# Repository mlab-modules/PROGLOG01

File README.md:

# PROGLOG01B - Small low-power open-source tool chain compatible FPGA

<!--- Lead --->
Module with a small programmable gate-array [ICE40UP5K](https://www.latticesemi.com/en/Products/FPGAandCPLD/iCE40UltraPlus).
<!--- ELead --->

The FPGA module compatible with fully open source toolchains like [symbiflow](https://symbiflow.github.io/).

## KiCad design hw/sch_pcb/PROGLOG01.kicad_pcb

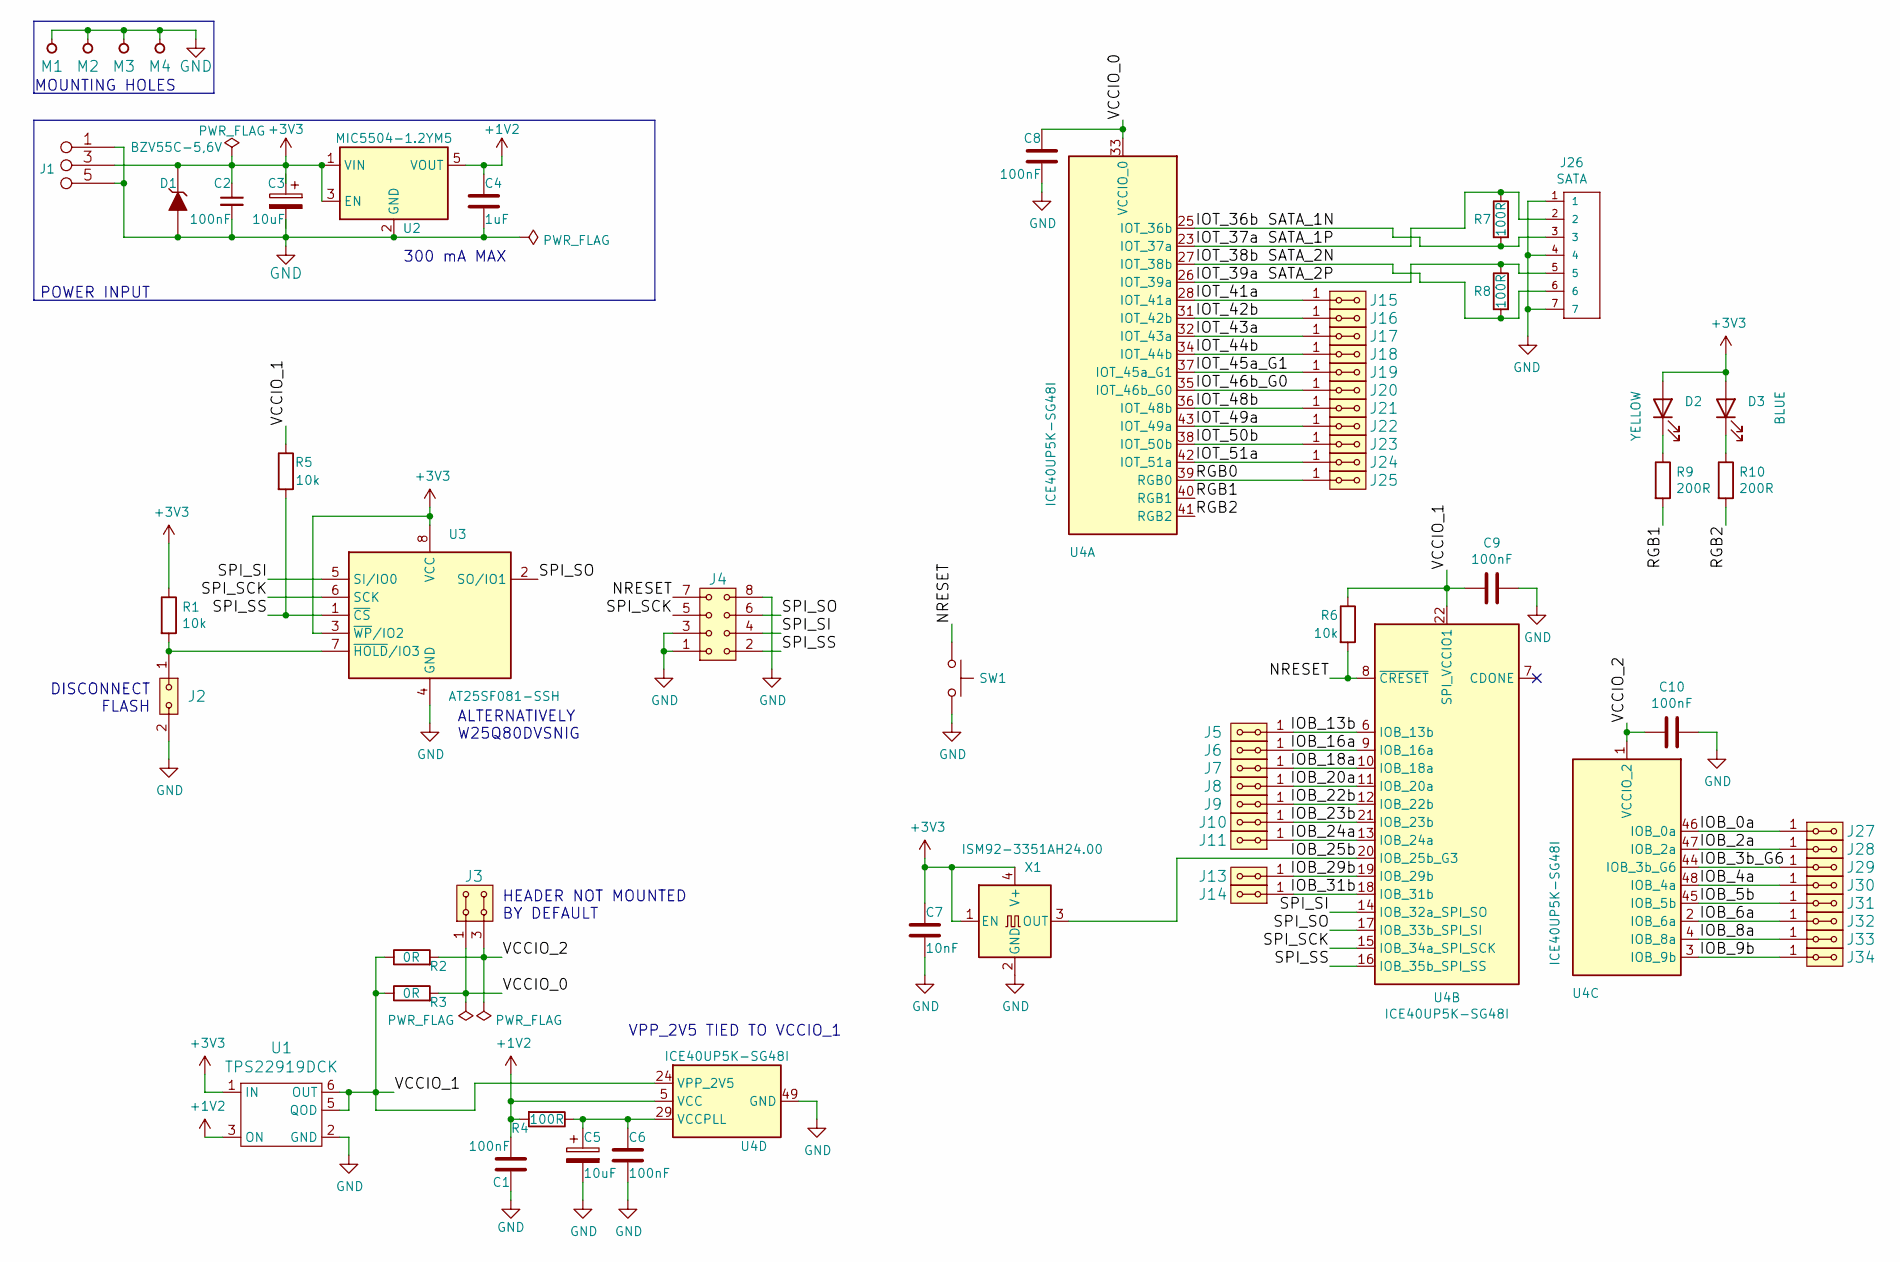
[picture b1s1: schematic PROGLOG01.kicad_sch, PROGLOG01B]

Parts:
C1, C2, C6, C8, C9, C10: 100nF; C_0805_2012Metric
C3, C5: 10uF; C_0805_2012Metric
C4: 1uF; C_0805_2012Metric
C7: 10nF; C_0805_2012Metric
D1: BZV55C-5,6V; Diode-MiniMELF_Standard
D2: YELLOW; LED_1206
D3: BLUE; LED_1206
J1: JUMP_3X2; Straight_2x03
J2: HEADER_2x01; Straight_2x01
J3: HEADER_2x02_PARALLEL; Straight_2x02
J4: HEADER_2x04; Straight_2x04
J5, J6, J7, J8, J9, J10, J11, J13, J14, J15, J16, J17, J18, J19, J20, J21, J22, J23, J24, J25, J27, J28, J29, J30, J31, J32, J33, J34: HEADER_2x01_PARALLEL; Straight_2x01
J26: SATA; MOLEX_67491-1030
M1, M2, M3, M4: HOLE; MountingHole_3mm
R1, R5, R6: 10k; R_0805_2012Metric
R2, R3: 0R; R_0805_2012Metric
R4, R7, R8: 100R; R_0805_2012Metric
R9, R10: 200R; R_0805_2012Metric
SW1: SW_Push; SW_PUSH_SMALL
U1: TPS22919DCK; SOT-363_SC-70-6_Handsoldering
U2: MIC5504-1.2YM5; SOT-23-5
U3: AT25SF081-SSH; SOIC-8_3.9x4.9mm_P1.27mm
U4: ICE40UP5K-SG48I; QFN-48-1EP_7x7mm_P0.5mm_EP5.6x5.6mm
X1: ISM92-3351AH24.00; Oscillator_SMD_EuroQuartz_XO91-4Pin_7.0x5.0mm

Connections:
+1V2: C1.2, C4.1, R4.2, U1.3 (ON), U2.5 (VOUT), U4.5 (VCC), U4.30 (VCC)
+3V3: C2.1, C3.1, C7.1, D1.1 (K), D2.2 (A), D3.2 (A), J1.3 (4), J1.4, R1.1, U1.1 (IN), U2.1 (VIN), U2.3 (EN), U3.3 (~WP/IO2), U3.8 (VCC), X1.1 (EN), X1.4 (V+)
/IOB_0a: J27.1, J27.2, U4.46 (IOB_0a)
/IOB_2a: J28.1, J28.2, U4.47 (IOB_2a)
/IOB_3b_G6: J29.1, J29.2, U4.44 (IOB_3b_G6)
/IOB_4a: J30.1, J30.2, U4.48 (IOB_4a)
/IOB_5b: J31.1, J31.2, U4.45 (IOB_5b)
/IOB_6a: J32.1, J32.2, U4.2 (IOB_6a)
/IOB_8a: J33.1, J33.2, U4.4 (IOB_8a)
/IOB_9b: J34.1, J34.2, U4.3 (IOB_9b)
/IOB_13b: J5.1, J5.2, U4.6 (IOB_13b)
/IOB_16a: J6.1, J6.2, U4.9 (IOB_16a)
/IOB_18a: J7.1, J7.2, U4.10 (IOB_18a)
/IOB_20a: J8.1, J8.2, U4.11 (IOB_20a)
/IOB_22b: J9.1, J9.2, U4.12 (IOB_22b)
/IOB_23b: J10.1, J10.2, U4.21 (IOB_23b)
/IOB_24a: J11.1, J11.2, U4.13 (IOB_24a)
/IOB_25b: U4.20 (IOB_25b_G3), X1.3 (OUT)
/IOB_29b: J13.1, J13.2, U4.19 (IOB_29b)
/IOB_31b: J14.1, J14.2, U4.18 (IOB_31b)
/IOT_36b: J26.3, R7.2, U4.25 (IOT_36b)
/IOT_37a: J26.2, R7.1, U4.23 (IOT_37a)
/IOT_38b: J26.6, R8.2, U4.27 (IOT_38b)
/IOT_39a: J26.5, R8.1, U4.26 (IOT_39a)
/IOT_41a: J15.1, J15.2, U4.28 (IOT_41a)
/IOT_42b: J16.1, J16.2, U4.31 (IOT_42b)
/IOT_43a: J17.1, J17.2, U4.32 (IOT_43a)
/IOT_44b: J18.1, J18.2, U4.34 (IOT_44b)
/IOT_45a_G1: J19.1, J19.2, U4.37 (IOT_45a_G1)
/IOT_46b_G0: J20.1, J20.2, U4.35 (IOT_46b_G0)
/IOT_48b: J21.1, J21.2, U4.36 (IOT_48b)
/IOT_49a: J22.1, J22.2, U4.43 (IOT_49a)
/IOT_50b: J23.1, J23.2, U4.38 (IOT_50b)
/IOT_51a: J24.1, J24.2, U4.42 (IOT_51a)
/NRESET: J4.7, R6.2, SW1.1, U4.8 (~CRESET)
/RGB0: J25.1, J25.2, U4.39 (RGB0)
/RGB1: R9.2, U4.40 (RGB1)
/RGB2: R10.2, U4.41 (RGB2)
/SPI_SCK: J4.5, U3.6 (SCK), U4.15 (IOB_34a_SPI_SCK)
/SPI_SI: J4.4, U3.5 (SI/IO0), U4.14 (IOB_32a_SPI_SO)
/SPI_SO: J4.6, U3.2 (SO/IO1), U4.17 (IOB_33b_SPI_SI)
/SPI_SS: J4.2, R5.2, U3.1 (~CS), U4.16 (IOB_35b_SPI_SS)
/VCCIO_0: C8.1, J3.1, J3.2, R3.2, U4.33 (VCCIO_0)
/VCCIO_1: C9.2, R2.1, R3.1, R5.1, R6.1, U1.5 (QOD), U1.6 (OUT), U4.22 (SPI_VCCIO1), U4.24 (VPP_2V5)
/VCCIO_2: C10.2, J3.3, J3.4, R2.2, U4.1 (VCCIO_2)
GND: C1.1, C2.2, C3.2, C4.2, C5.2, C6.2, C7.2, C8.2, C9.1, C10.1, D1.2 (A), J1.1 (2), J1.2, J1.5 (6), J1.6, J2.2, J4.1, J4.3, J4.8, J26.1, J26.4, J26.7, M1.1, M2.1, M3.1, M4.1, SW1.2, U1.2 (GND), U2.2 (GND), U3.4 (GND), U4.49 (GND), X1.2 (GND)
unnamed: C5.1, C6.1, R4.1, U4.29 (VCCPLL)
unnamed: D2.1 (K), R9.1
unnamed: D3.1 (K), R10.1
unnamed: J2.1, R1.2, U3.7 (~HOLD/IO3)

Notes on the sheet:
HEADER NOT MOUNTED BY DEFAULT
VPP_2V5 TIED TO VCCIO_1
MOUNTING HOLES
DISCONNECT FLASH
300 mA MAX
POWER INPUT
ALTERNATIVELY W25Q80DVSNIG

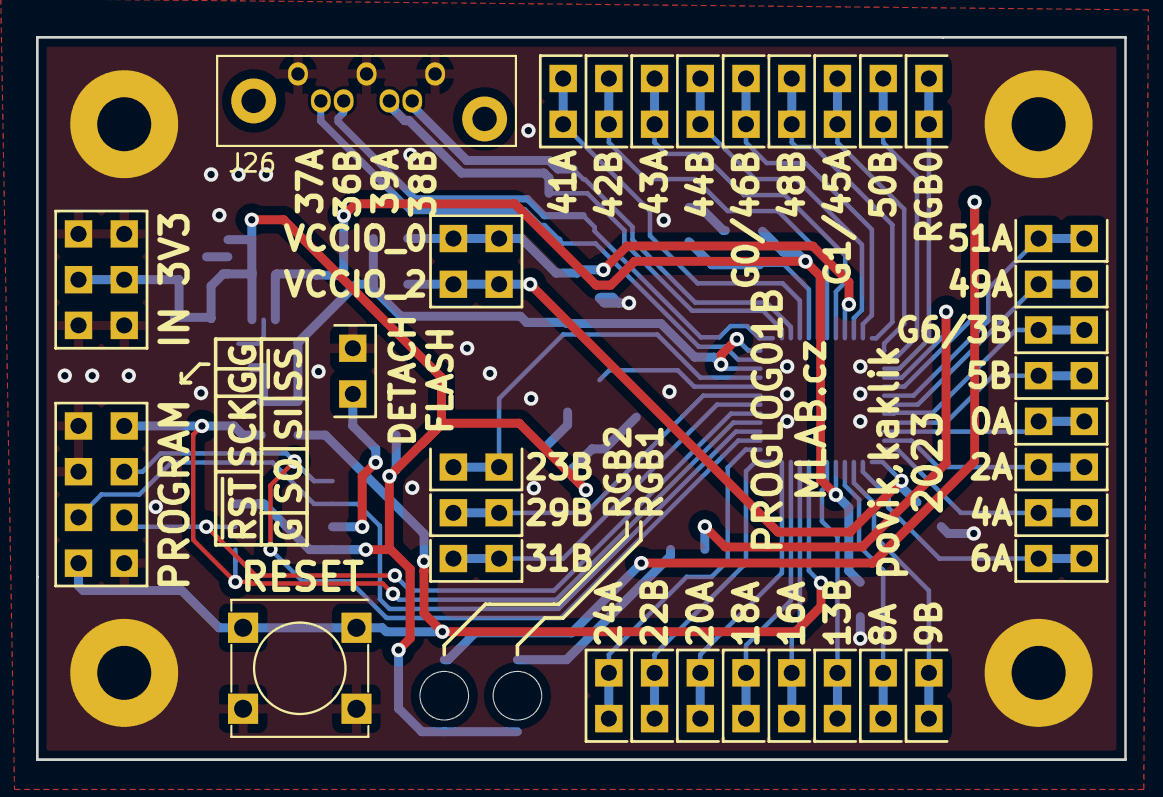
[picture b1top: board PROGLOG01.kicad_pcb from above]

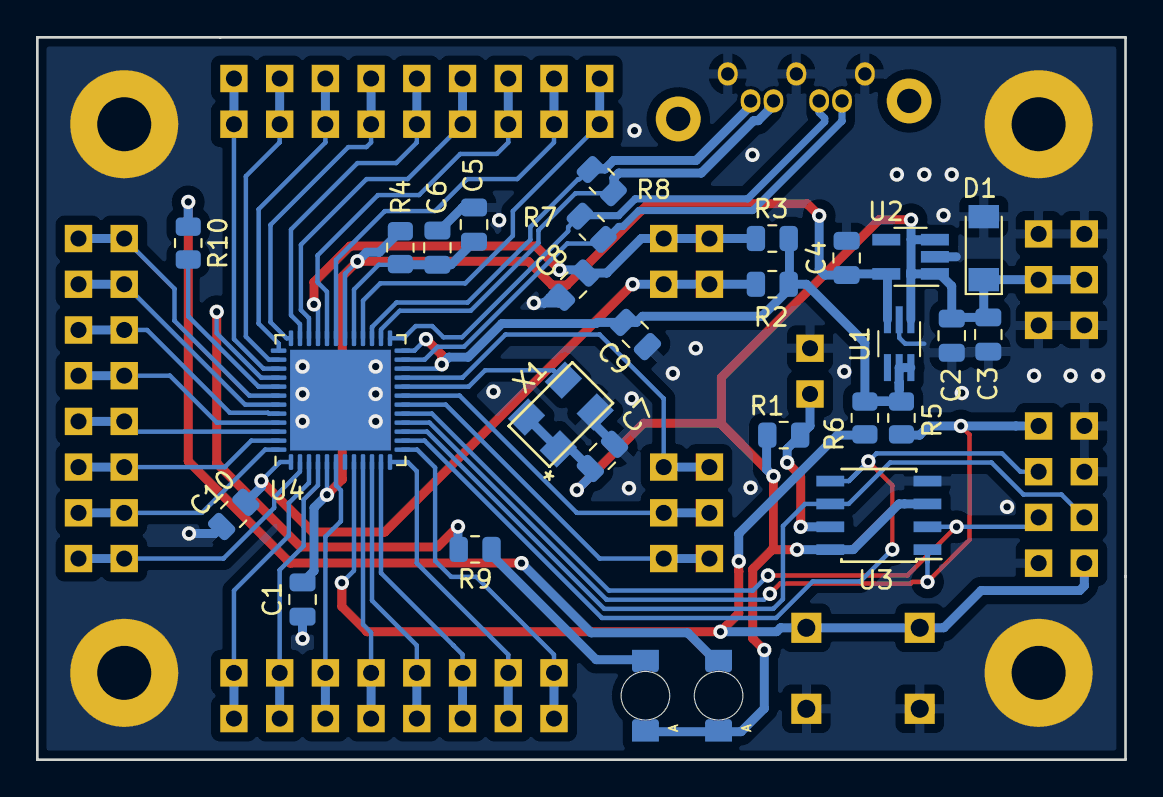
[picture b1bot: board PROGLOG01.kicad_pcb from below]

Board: 2 copper layers, 60.5 x 40.1 mm, 66 parts (28 on the bottom side), 50 nets.

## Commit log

2019-09-25 Initialize PROGLOG01A with a preliminary schema
2019-09-25 Fix supplies in PROGLOG01A schematics
2019-09-25 Fix supplies in PROGLOG01A schematic
2019-10-09 Progress on PROGLOG01A
2019-10-13 Make changes to PROGLOG01A schematic
2019-10-14 Change footprints and make a minor fix
2019-10-22 Start drawing, make some fixes to schematic
2019-10-28 Progress on drawing, change schematic
2019-11-04 Fix layout issues
2019-11-08 Generovana vyrobni data
2019-11-14 Uprava dat pro osazovani
2019-11-30 [MLABweb] Documentation edits; PROGLOG01A
2020-01-22 Edit for USBI2C01A
2020-05-04 The basic photos of new modules.
2020-05-04 Add photos of programmer connection.
2022-02-13 Documentation update. Project updated to kicad 6.0.1.
2022-02-13 repository cleanup Removing old KiCAD project files.
2022-04-06 automated commit; add github actions
2022-04-06 Update actions products
2022-11-16 Start a work on updated, fixed version.
2023-02-14 update actions
2023-02-14 Update metadata files
2023-02-19 Rename project to revision neutral name.
2023-02-19 Update submodule.
2023-02-19 Manually update actions.
2023-02-19 Update project and documentation.
2023-02-19 Fix unconnected tracks DRC errors.
2023-02-19 Repair #1 in schematics.
2023-02-19 Fix #1 Layout improvement vias position improvement.
2023-02-20 Update workflow files
2023-03-02 Imrove layout - avoid sharp edges.
2023-03-03 Update footprints from library. Improve bottom silkscreen.
2023-03-03 Resolve DRC errors in silkscreen.
2023-03-03 Resolve silkscreen and layout issues.
2023-03-03 Fix wrong UST_ID assigned.
2023-03-03 Update actions scripts Cleanup B.Fab layer.
2023-03-03 Update workflows manually.
2023-03-04 Update schematics symbols.
2023-03-04 Add a link to datasheet.
2023-03-04 Improve B.Fab readability.
2023-07-05 automated commit; rename source files to new naming convence
2023-09-16 Update image to image_title
2023-09-16 Update status
2023-09-17 Update metadata.yaml
    select title_image
2023-09-17 Delete PROGLOG01A.json
    delete file without useful data.
